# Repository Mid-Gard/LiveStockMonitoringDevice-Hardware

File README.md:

# LiveStock Monitoring Hardware Material

This repository contains the Kikad PCB design and arduino programs for the microcontroller used in the design.

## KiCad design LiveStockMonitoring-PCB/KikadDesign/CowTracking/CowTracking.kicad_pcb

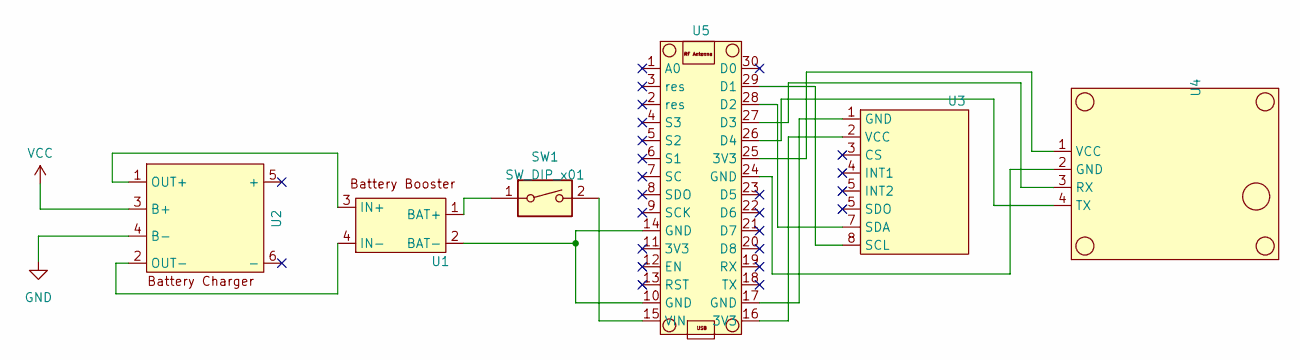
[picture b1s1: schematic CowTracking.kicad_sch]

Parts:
SW1: SW_DIP_x01
U1: HW-168_BatteryBooster
U2: BatteryCharger
U3: Accelerometer
U4: GY-NE06MV2
U5: NodeMCU1.0(12-E)

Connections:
GND: U2.4 (B-)
unnamed: SW1.1, U1.1 (BAT+)
unnamed: U1.2 (BAT-), U5.10 (GND), U5.14 (GND)
unnamed: U1.3 (IN+), U2.1 (OUT+)
unnamed: U1.4 (IN-), U2.2 (OUT-)
unnamed: U3.1 (GND), U5.17 (GND)
unnamed: U3.8 (SCL), U5.29 (D1)
unnamed: U3.7 (SDA), U5.28 (D2)
unnamed: U3.2 (VCC), U5.16 (3V3)
unnamed: U4.2 (GND), U5.24 (GND)
unnamed: U4.3 (RX), U5.27 (D3)
unnamed: U4.4 (TX), U5.26 (D4)
unnamed: U4.1 (VCC), U5.25 (3V3)
unnamed: SW1.2, U5.15 (VIN)
VCC: U2.3 (B+)

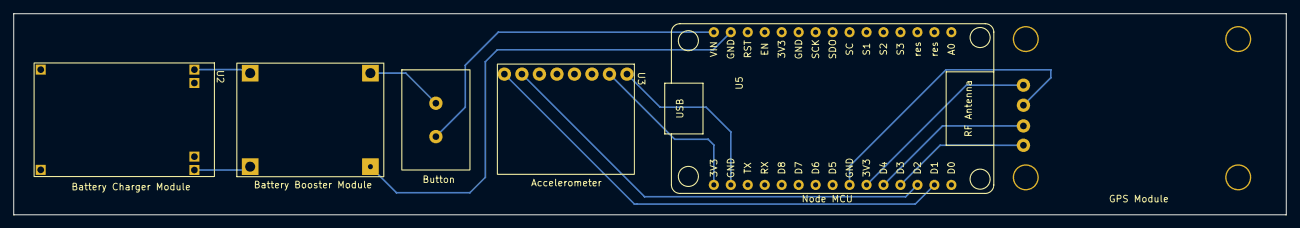
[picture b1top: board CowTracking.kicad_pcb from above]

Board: 2 copper layers, 190.5 x 30.1 mm, 6 parts (1 on the bottom side), 13 nets.

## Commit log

2023-12-28 Added Kikad PCB Design
2023-12-28 Added NodeMCU Arduino codes
2023-12-28 Added readme
2023-12-28 readme update
